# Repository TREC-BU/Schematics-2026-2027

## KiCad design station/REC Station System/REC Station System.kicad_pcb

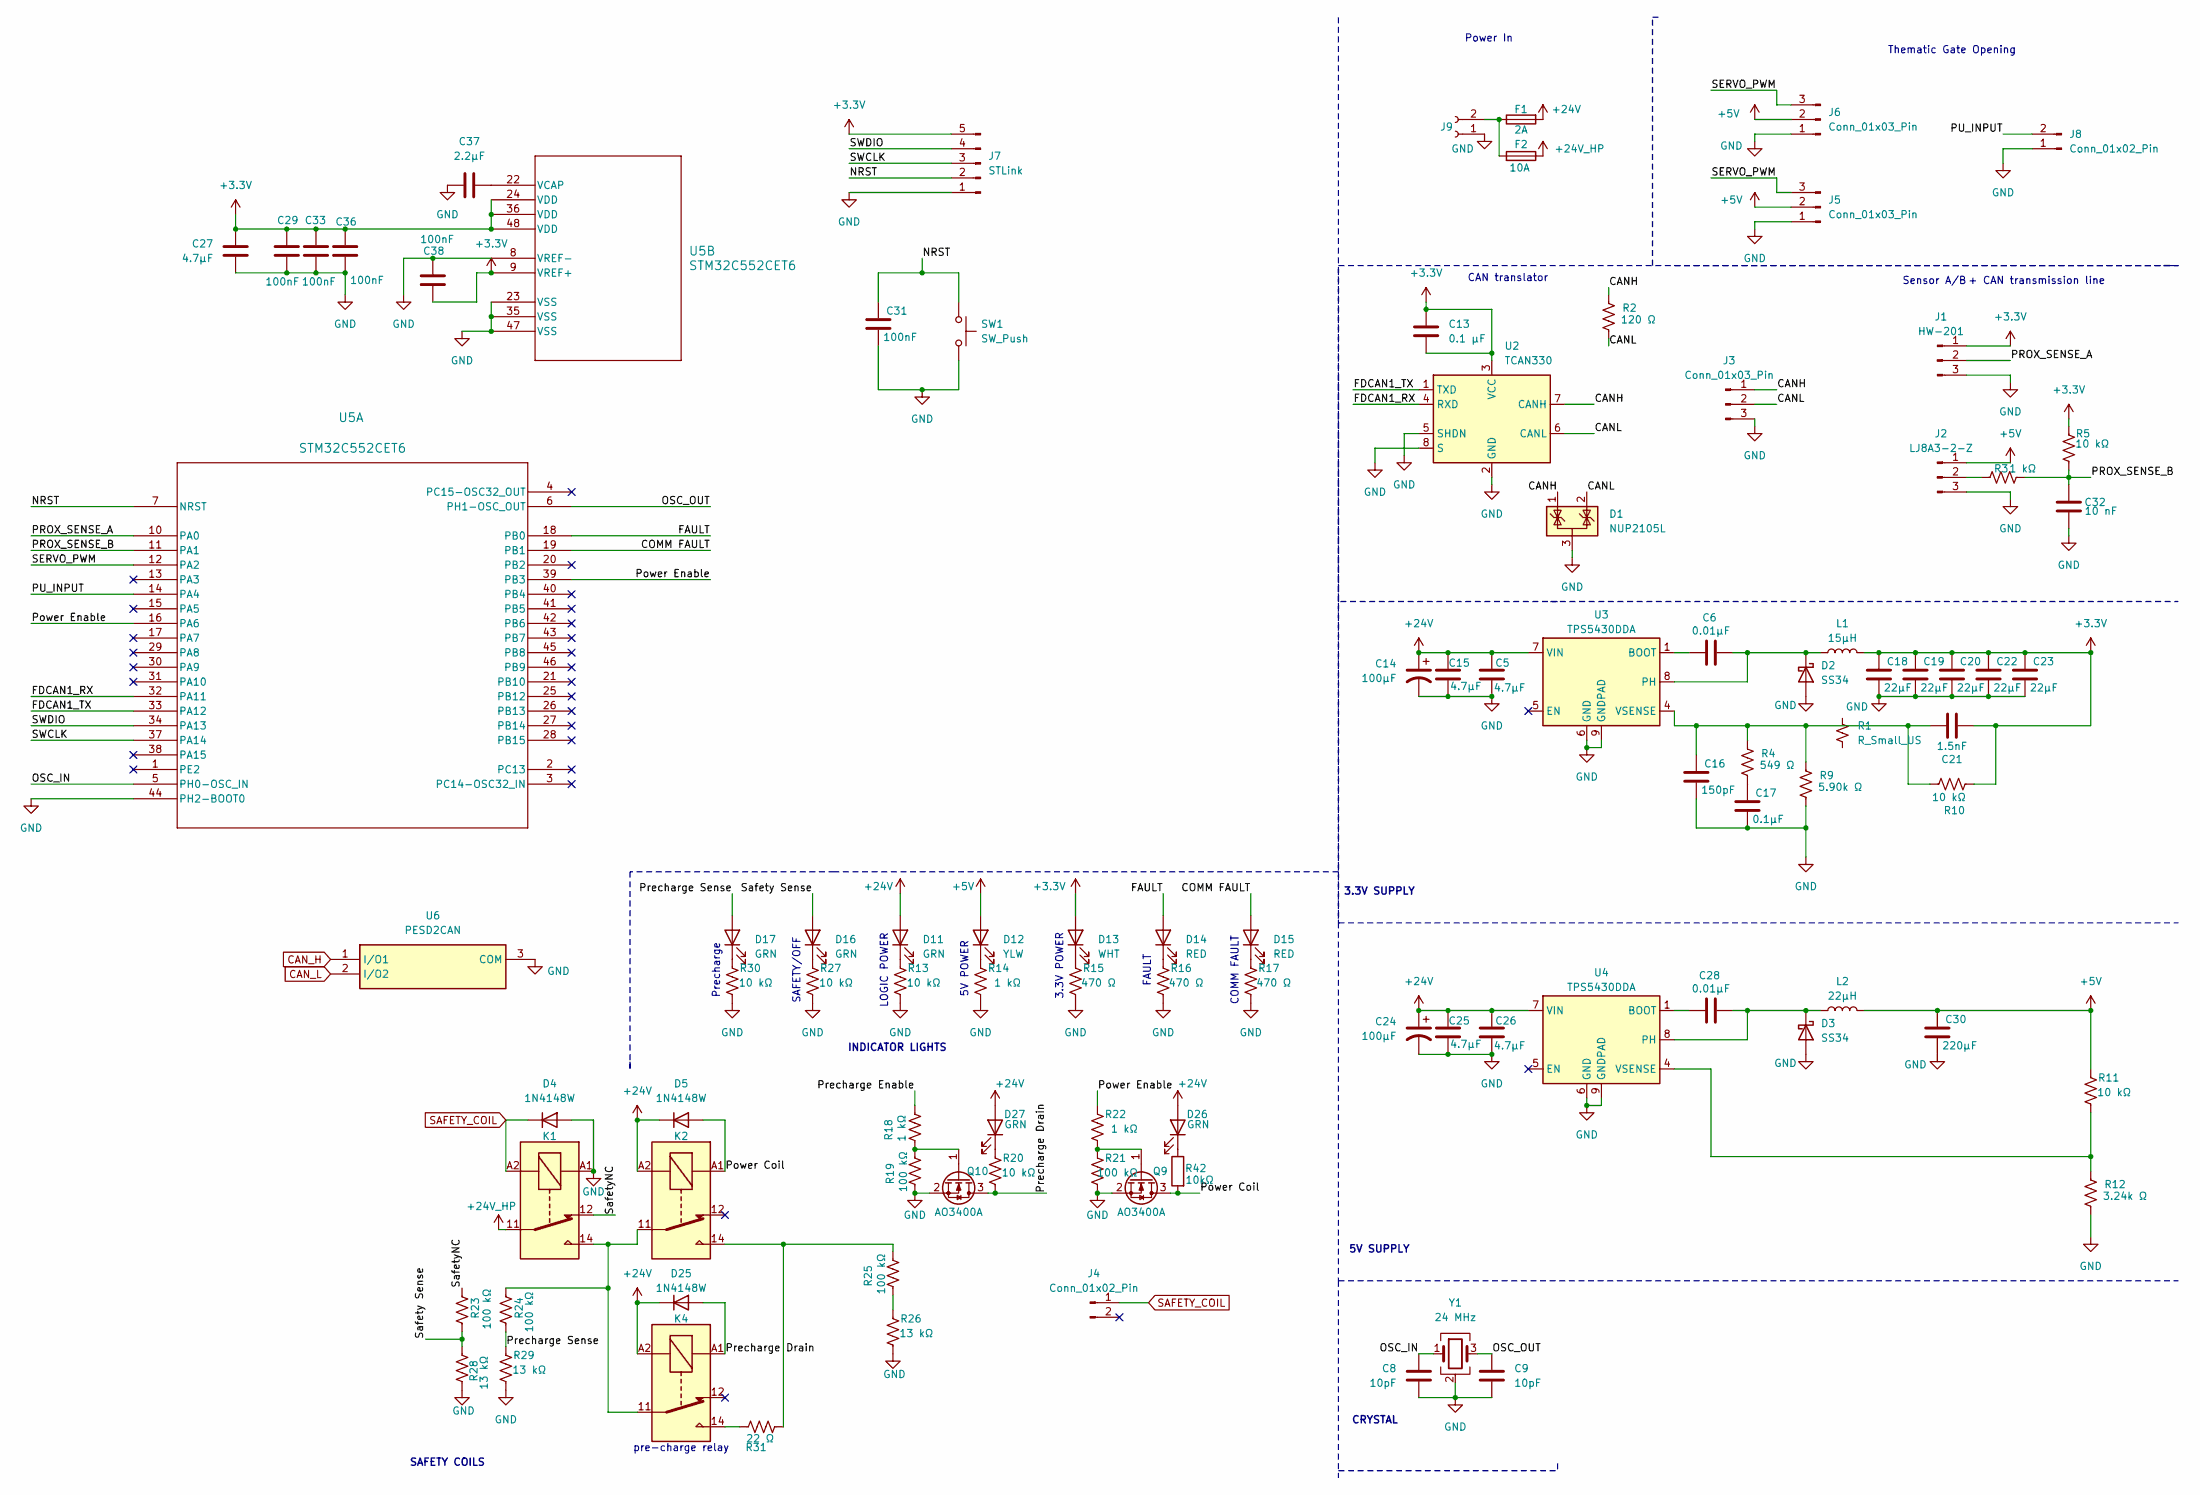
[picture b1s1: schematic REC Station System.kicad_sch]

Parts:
C5, C15, C25, C26, C27: 4.7µF; C_0805_2012Metric
C6: 0.01µF; C_0805_2012Metric
C8, C9: 10pF; C_0402_1005Metric
C13: 0.1 µF; C_0805_2012Metric
C14, C24: 100µF; CP_Elec_8x10.5
C16: 150pF; C_0805_2012Metric
C17: 0.1µF; C_0805_2012Metric
C18, C19, C20, C22, C23: 22µF; C_1210_3225Metric
C21: 1.5nF; C_0805_2012Metric
C28: 0.01µF; C_1210_3225Metric
C29, C33, C36, C38: 100nF; C_1210_3225Metric
C30: 220µF; CP_EIA-7343-30_AVX-N
C31: 100nF; C_0805_2012Metric
C32: 10 nF; C_0805_2012Metric
C37: 2.2µF; C_0805_2012Metric
D1: NUP2105L; SOT-23
D2, D3: SS34; D_SMA
D4, D5, D25: 1N4148W; D_SOD-123
D11, D16, D17, D26, D27: GRN; LED_0603_1608Metric
D12: YLW; LED_0603_1608Metric
D13: WHT; LED_0603_1608Metric
D14, D15: RED; LED_0603_1608Metric
F1: 2A; Fuseholder_Blade_Mini_Keystone_3568
F2: 10A; Fuseholder_Blade_Mini_Keystone_3568
J1: HW-201; PinHeader_1x03_P2.54mm_Vertical
J2: LJ8A3-2-Z; PinHeader_1x03_P2.54mm_Vertical
J3: Conn_01x03_Pin; TerminalBlock_Phoenix_MKDS-1,5-3-5.08_1x03_P5.08mm_Horizont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
J4: Conn_01x02_Pin; TerminalBlock_Phoenix_MKDS-1,5-2_1x02_P5.00mm_Horizontal
J5, J6: Conn_01x03_Pin; PinHeader_1x03_P2.54mm_Vertical
J7: STLink; PinHeader_1x05_P2.54mm_Vertical
J8: Conn_01x02_Pin; JST_XH_B2B-XH-A_1x02_P2.50mm_Vertical
J9: Conn_01x02_Socket; AMASS_XT30PW-F_1x02_P2.50mm_Horizontal
K1, K2, K4: Relay_SPDT; Relay_SPDT_Omron-G5LE-1
L1: 15µH; L_Bourns_SRR1260
L2: 22µH; L_Bourns_SRP1245A
Q9, Q10: AO3400A; SOT-23
R1: R_Small_US; R_Axial_Power_L20.0mm_W6.4mm_P25.40mm
R2: 120 Ω; R_0805_2012Metric
R3, R14, R18, R22: 1 kΩ; R_0805_2012Metric
R4: 549 Ω; R_0805_2012Metric
R5, R10, R11, R13, R20, R27, R30: 10 kΩ; R_0805_2012Metric
R9: 5.90k Ω; R_0805_2012Metric
R12: 3.24k Ω; R_0805_2012Metric
R15, R16, R17: 470 Ω; R_0805_2012Metric
R19, R21, R23, R24, R25: 100 kΩ; R_0805_2012Metric
R26, R28, R29: 13 kΩ; R_0805_2012Metric
R31: 22 Ω; R_0805_2012Metric
R42: 10kΩ; R_0603_1608Metric
SW1: SW_Push; SW_SPST_PTS645Sx43SMTR92
U2: TCAN330; D0008A_N
U3, U4: TPS5430DDA; TI_SO-PowerPAD-8_ThermalVias
U5: STM32C552CET6; LQFP-48_7x7mm_P0.5mm
U6: PESD2CAN; SOT-23
Y1: 24 MHz; Crystal_SMD_3225-4Pin_3.2x2.5mm

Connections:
+3.3V: C13.1, C13.2, C18.1, C19.1, C20.1, C21.2, C22.1, C23.1, C27.1, C29.1, C33.1, C36.1, C38.2, D13.2 (A), J1.1, J7.5, L1.2, R5.2, R10.1, U2.3 (VCC), U5.9 (VREF+), U5.24 (VDD), U5.36 (VDD), U5.48 (VDD)
+5V: C30.1, D12.2 (A), J2.1, J5.2, J6.2, L2.2, R11.2
+24V: C5.1, C14.1, C15.1, C24.1, C25.1, C26.1, D5.1 (K), D11.2 (A), D25.1 (K), D26.2 (A), D27.2 (A), F1.2, K2.A2, K4.A2, U3.7 (VIN), U4.7 (VIN)
+24V_HP: F2.1, K1.11
/CANH: D1.1 (K), J3.1, R2.1, U2.7 (CANH)
/CANL: D1.2 (K), J3.2, R2.2, U2.6 (CANL)
/COMM FAULT: D15.2 (A), U5.19 (PB1)
/FAULT: D14.2 (A), U5.18 (PB0)
/FDCAN1_RX: U2.4 (RXD), U5.32 (PA11)
/FDCAN1_TX: U2.1 (TXD), U5.33 (PA12)
/NRST: C31.1, J7.2, SW1.1, U5.7 (NRST)
/OSC_IN: C8.2, U5.5 (PH0-OSC_IN), Y1.1
/OSC_OUT: C9.2, U5.6 (PH1-OSC_OUT), Y1.3
/PROX_SENSE_A: J1.2, U5.10 (PA0)
/PROX_SENSE_B: C32.2, R3.2, R5.1, U5.11 (PA1)
/PU_INPUT: J8.2, U5.14 (PA4)
/Power Coil: D5.2 (A), K2.A1, Q9.3 (D), R42.2
/Power Enable: R22.2, U5.16 (PA6), U5.39 (PB3)
/Precharge Drain: D25.2 (A), K4.A1, Q10.3 (D), R20.1
/Precharge Enable: R18.2
/Precharge Sense: D17.2 (A), R24.1, R29.2
/SERVO_PWM: J5.3, J6.3, U5.12 (PA2)
/SWCLK: J7.3, U5.37 (PA14)
/SWDIO: J7.4, U5.34 (PA13)
/Safety Sense: D16.2 (A), R23.1, R28.2
/SafetyNC: K1.12, R23.2
CAN_H: U6.1 (I/O1)
CAN_L: U6.2 (I/O2)
GND: C5.2, C8.1, C9.1, C14.2, C15.2, C16.2, C17.2, C18.2, C19.2, C20.2, C22.2, C23.2, C24.2, C25.2, C26.2, C27.2, C29.2, C30.2, C31.2, C32.1, C33.2, C36.2, C37.1, C38.1, D1.3 (A), D2.2 (A), D3.2 (A), D4.2 (A), J1.3, J2.3, J3.3, J5.1, J6.1, J7.1, J8.1, J9.1, K1.A1, Q9.2 (S), Q10.2 (S), R9.2, R12.2, R13.1, R14.1, R15.1, R16.1, R17.1, R19.1, R21.1, R26.1, R27.1, R28.1, R29.1, R30.1, SW1.2, U2.2 (GND), U2.5 (SHDN), U2.8 (S), U3.6 (GND), U3.9 (GNDPAD), U4.6 (GND), U4.9 (GNDPAD), U5.8 (VREF-), U5.23 (VSS), U5.35 (VSS), U5.44 (PH2-BOOT0), U5.47 (VSS), U6.3 (COM), Y1.2 (G), Y1.4 (G)
unnamed: C17.1, R4.2
unnamed: C6.2, D2.1 (K), L1.1, U3.8 (PH)
unnamed: C28.2, D3.1 (K), L2.1, U4.8 (PH)
unnamed: D11.1 (K), R13.2
unnamed: D12.1 (K), R14.2
unnamed: D13.1 (K), R15.2
unnamed: D14.1 (K), R16.2
unnamed: D15.1 (K), R17.2
unnamed: D16.1 (K), R27.2
unnamed: D17.1 (K), R30.2
unnamed: D26.1 (K), R42.1
unnamed: D27.1 (K), R20.2
unnamed: J2.2, R3.1
unnamed: F1.1, F2.2, J9.2
unnamed: K1.14, K2.11, K4.11, R24.2
unnamed: K2.14, R25.2, R31.2
unnamed: K4.14, R31.1
unnamed: Q9.1 (G), R21.2, R22.1
unnamed: Q10.1 (G), R18.1, R19.2
unnamed: R25.1, R26.2
unnamed: C6.1, U3.1 (BOOT)
unnamed: C16.1, C21.1, R4.1, R9.1, R10.2, U3.4 (VSENSE)
unnamed: C28.1, U4.1 (BOOT)
unnamed: R11.1, R12.1, U4.4 (VSENSE)
unnamed: C37.2, U5.22 (VCAP)
SAFETY_COIL: D4.1 (K), J4.1 (Pin_1_1), K1.A2

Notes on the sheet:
SAFETY COILS
+ CAN transmission line
5V POWER
CRYSTAL
CAN translator
SAFETY/OFF
Precharge
Thematic Gate Opening
LOGIC POWER
3.3V POWER
3.3V SUPPLY
FAULT
INDICATOR LIGHTS
5V SUPPLY
Power In
pre-charge relay
Sensor A/B
COMM FAULT

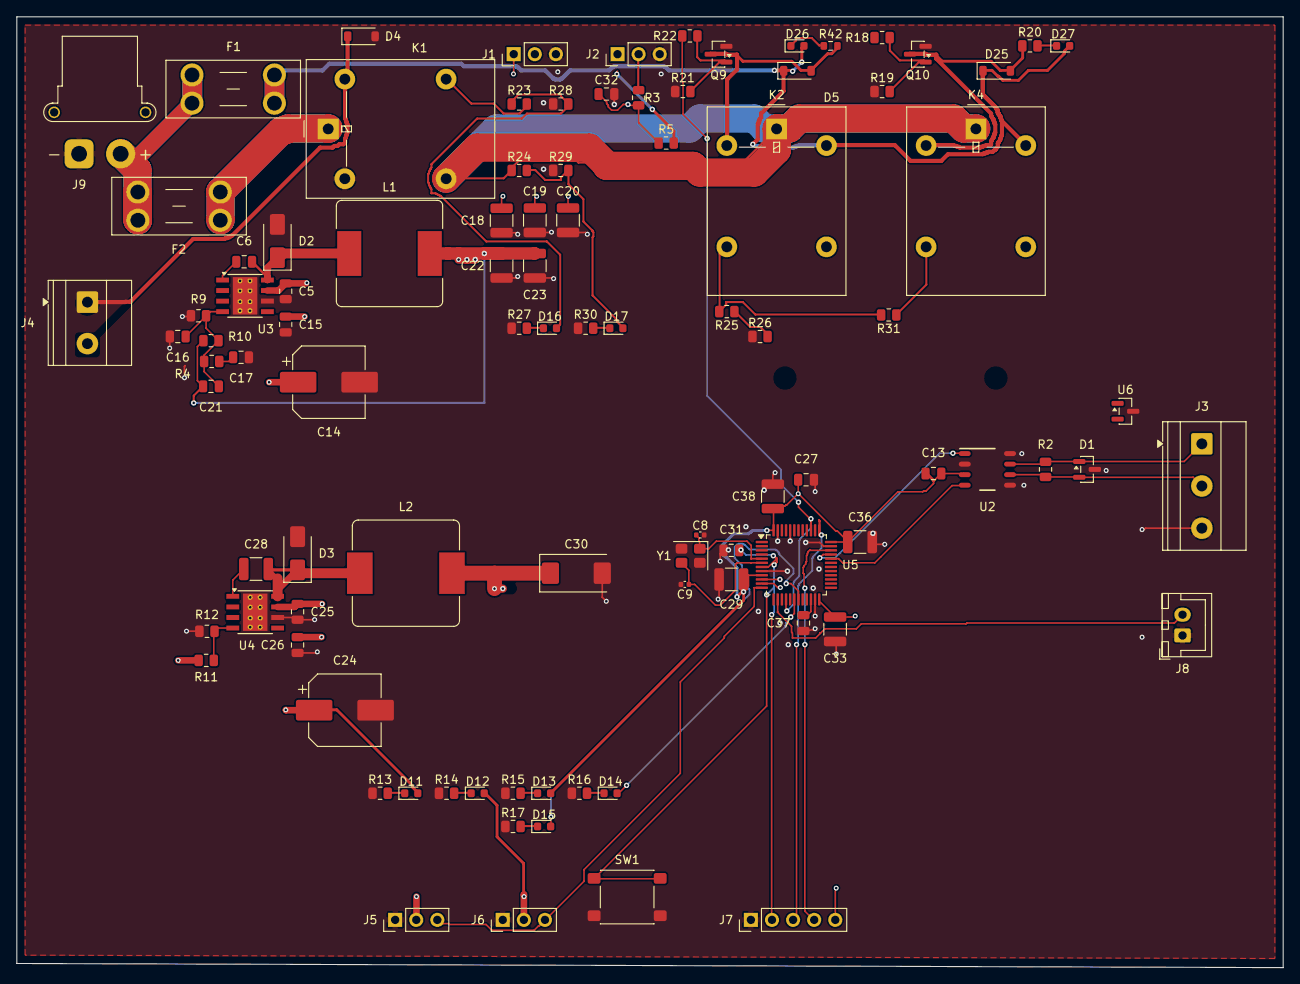
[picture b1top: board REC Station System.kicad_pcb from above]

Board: 4 copper layers, 152.5 x 114.5 mm, 96 parts (0 on the bottom side), 52 nets.

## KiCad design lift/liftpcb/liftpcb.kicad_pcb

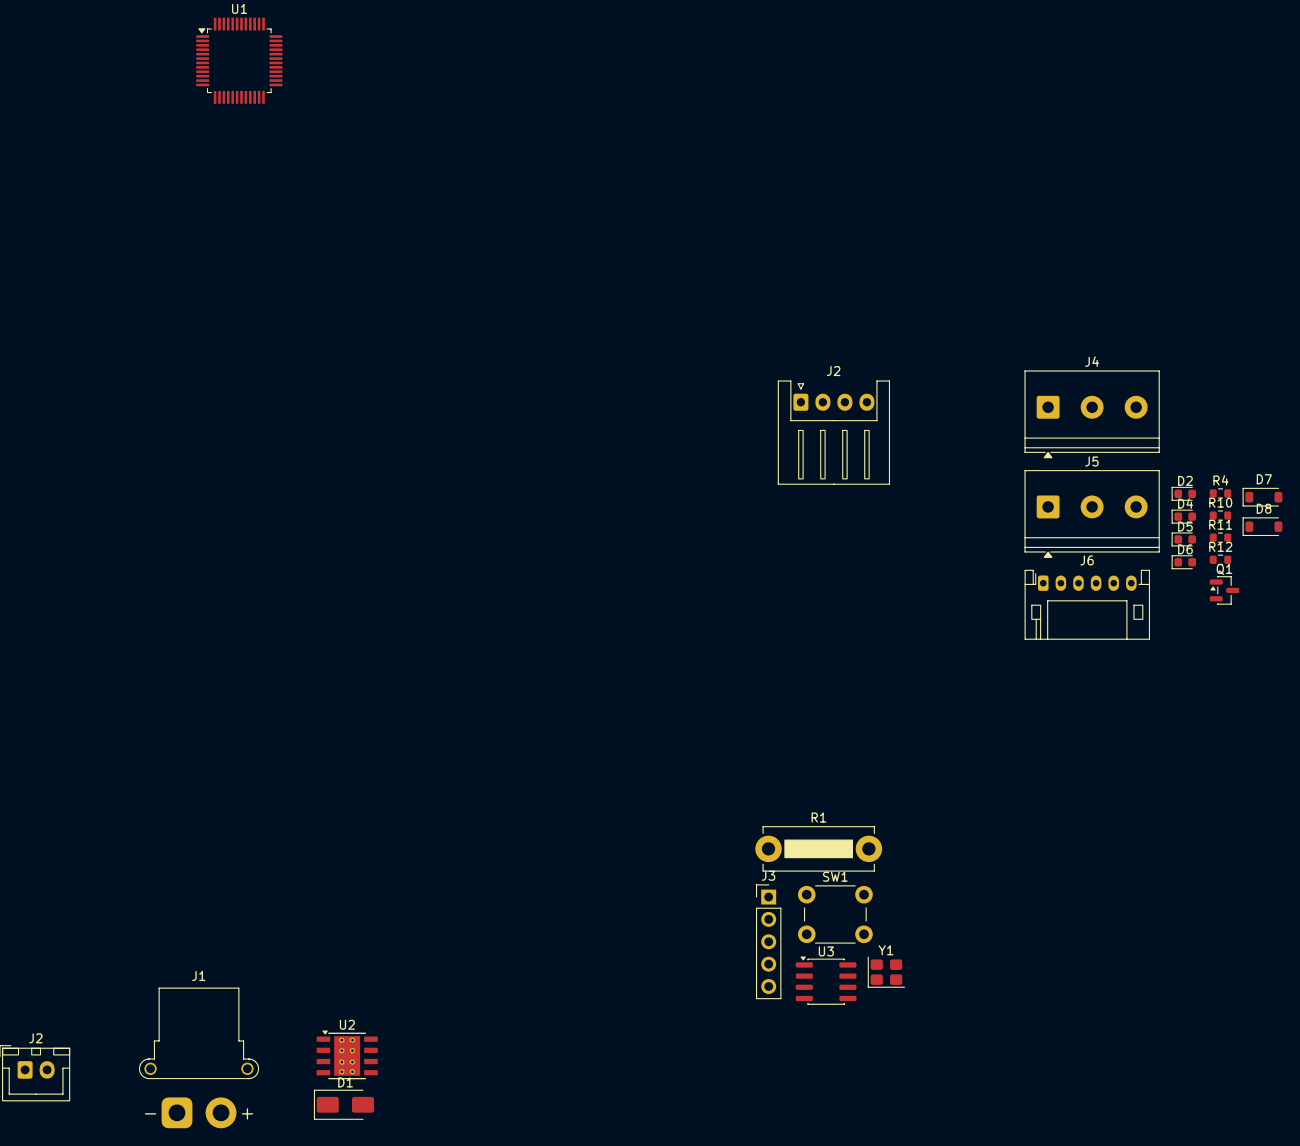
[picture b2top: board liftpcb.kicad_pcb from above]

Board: 2 copper layers, 25 parts (0 on the bottom side), 24 nets, no tracks yet.

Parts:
D1: SS34; D_SMA
D2: GRN; LED_0603_1608Metric
D4: YLW; LED_0603_1608Metric
D5: WHT; LED_0603_1608Metric
D6: RED; LED_0603_1608Metric
D7, D8: 1N4148W; D_SOD-123
J1: Conn_01x02_Socket; AMASS_XT30PW-F_1x02_P2.50mm_Horizontal
J2: Conn_01x02_Socket; JST_XH_B2B-XH-A_1x02_P2.50mm_Vertical
J2#2: Conn_01x04_Socket; JST_XH_S4B-XH-A_1x04_P2.50mm_Horizontal
J3: Conn_01x05_Pin; PinHeader_1x05_P2.54mm_Vertical
J4, J5: Screw_Terminal_01x03; TerminalBlock_Phoenix_PT-1,5-3-5.0-H_1x03_P5.00mm_Horizontal
J6: Conn_01x06_Socket; JST_PH_S6B-PH-K_1x06_P2.00mm_Horizontal
Q1: MMBT3904; SOT-23
R1: 120Ω; R_Bare_Metal_Element_L12.4mm_W4.8mm_P11.40mm
R4, R10: 10kΩ; R_0603_1608Metric
R11: 100Ω; R_0603_1608Metric
R12: 470Ω; R_0603_1608Metric
SW1: SW_Push; SW_PUSH_6mm_H5mm
U1: STM32C552CET6; LQFP-48_7x7mm_P0.5mm
U2: TPS5430DDA; TI_SO-PowerPAD-8_ThermalVias
U3: SN65HVD230DR; SOIC-8_3.9x4.9mm_P1.27mm
Y1: 24 MHz; Crystal_SMD_3225-4Pin_3.2x2.5mm

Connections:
+3.3V: J3.1, J6.1, U1.9 (VREF+), U1.24 (VDD), U1.36 (VDD), U1.48 (VDD), U3.3 (VCC)
+24V: D2.2 (A), D8.1 (K), J1.2, U2.7 (VIN)
CAN_H: J2#2.4, R1.1, U3.7 (CANH)
CAN_L: J2#2.3, R1.2, U3.6 (CANL)
CAN_RX: U1.32 (PA11), U3.4 (R)
CAN_TX: U1.33 (PA12), U3.1 (D)
COMM_LED: D5.2 (A), U1.18 (PB0)
FAULT_LED: D6.2 (A), U1.19 (PB1)
GND: D1.2 (A), D7.2 (A), J1.1, J3.5, J4.1, J5.2, J6.6, Q1.2 (E), R4.2, R10.2, R11.2, R12.2, SW1.1, U1.8 (VREF-), U1.23 (VSS), U1.35 (VSS), U1.47 (VSS), U2.6 (GND), U2.9 (GNDPAD), U3.2 (GND), U3.8 (Rs), Y1.2 (G), Y1.4 (G)
NRST: J3.3, SW1.2, U1.7 (NRST)
unnamed: D1.1 (K), U2.8 (PH)
unnamed: D2.1 (K), R4.1
unnamed: D4.1 (K), R10.1
unnamed: D5.1 (K), R11.1
unnamed: D6.1 (K), R12.1
OSC_IN: U1.5 (PH0-OSC_IN), Y1.1
OSC_OUT: U1.6 (PH1-OSC_OUT), Y1.3
PWR_COIL: D8.2 (A), Q1.3 (C)
S+24V: D4.2 (A), J5.3
SAFETY_COIL: D7.1 (K), J2#2.1
SWCLK: J3.2, U1.37 (PA14)
SWDIO: J3.4, U1.34 (PA13)
UART1_RX: J4.2, U1.31 (PA10)
UART1_TX: J4.3, U1.38 (PA15)
